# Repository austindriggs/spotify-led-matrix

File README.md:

# Welcome to my first project!

My name is Austin Driggs and I am an Electrical Engineering student at WVU.
Please check out my [LinkedIn](https://www.linkedin.com/in/austindriggs/)!

This project uses an ESP32 microcontroller to display my "Now Playing" songs from Spotify onto an LED matrix panel, along with some added features.

### Purpose

The purpose of this project is to of course learn some new technical skills, but to also practice things related to my career in open sourced coding/projects and project management. I want to document everything along the way to cite sources from what I've learned, decisions I've made, and also to track time. 

## Important Information

### Project Epic

Please see the [Project Epic](https://github.com/austindriggs/spotify-led-matrix/issues/16) for a list of all issues and tasks completed and the order they were completed in.

### Hardware

The KiCAD project is for v7.

### Software

I plan to use python.

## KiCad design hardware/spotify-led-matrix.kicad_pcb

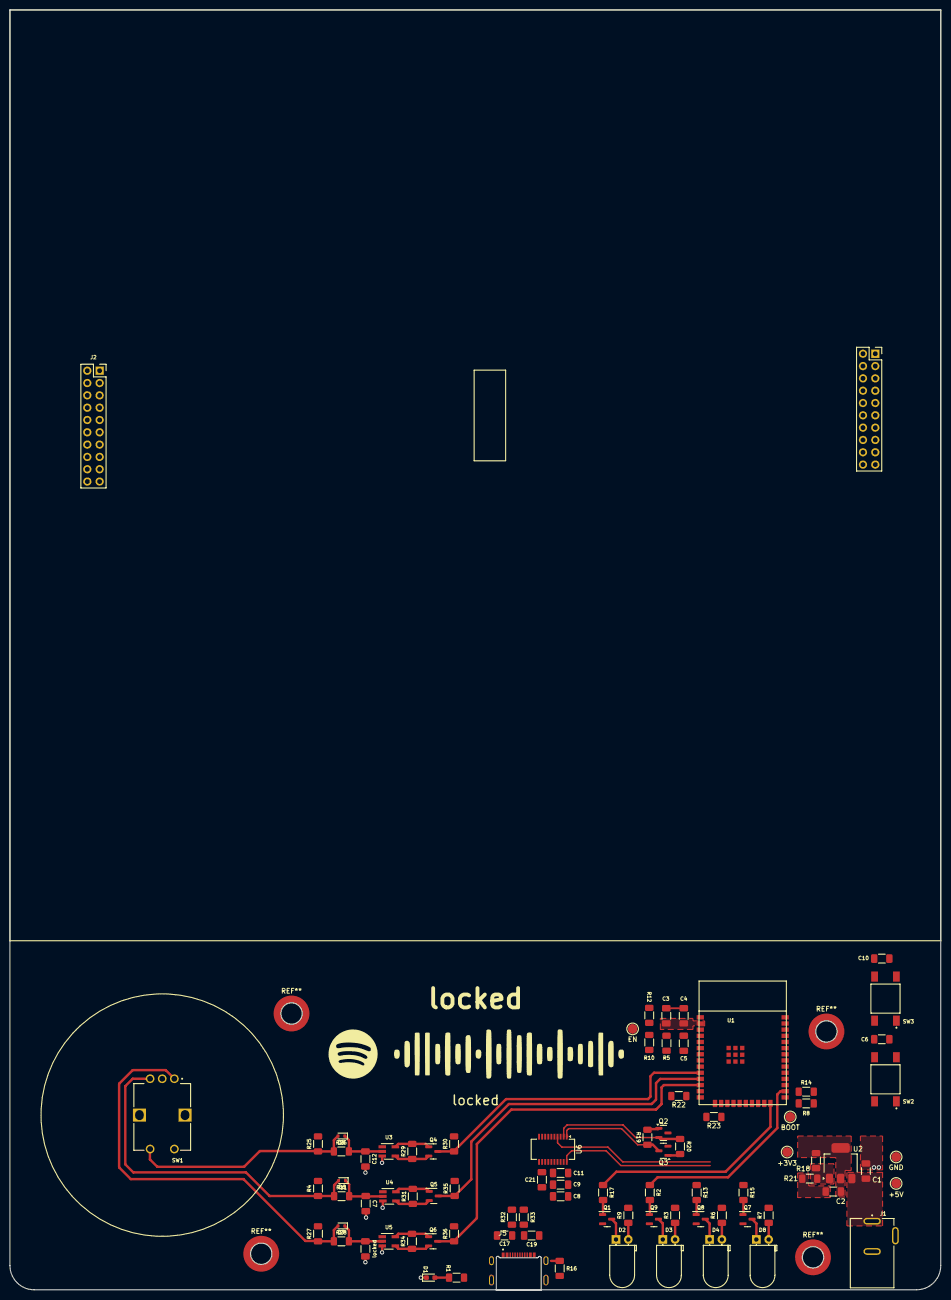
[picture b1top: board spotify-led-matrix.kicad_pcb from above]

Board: 2 copper layers, 192.0 x 264.1 mm, 86 parts (0 on the bottom side), 68 nets.

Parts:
C1, C2: 10uF; C_1206_3216Metric_Pad1.33x1.80mm_HandSolder
C3: 22uF; C_1206_3216Metric_Pad1.33x1.80mm_HandSolder
C4, C6, C7, C10, C12: 0.1uF; C_1206_3216Metric_Pad1.33x1.80mm_HandSolder
C5: 1uF; C_1206_3216Metric_Pad1.33x1.80mm_HandSolder
C8: 4.7uF; C_1206_3216Metric_Pad1.33x1.80mm_HandSolder
C9, C11, C21: 100nF; C_1206_3216Metric_Pad1.33x1.80mm_HandSolder
C17, C19: 47pF; C_1206_3216Metric_Pad1.33x1.80mm_HandSolder
D1: USB; LED_0603_1608Metric_Pad1.05x0.95mm_HandSolder
D2: DEV; LED_D5.0mm_Horizontal_O1.27mm_Z9.0mm
D3: VOLUME; LED_D5.0mm_Horizontal_O1.27mm_Z9.0mm
D4: BRIGHTNESS; LED_D5.0mm_Horizontal_O1.27mm_Z9.0mm
D5, D6, D7: D; D_SOD-523
D8: MODES; LED_D5.0mm_Horizontal_O1.27mm_Z9.0mm
J1: +5V; 54-00166
J2: DISPLAY_IN; PinSocket_2x10_P2.54mm_Vertical
J4: DISPLAY_OUT; PinSocket_2x10_P2.54mm_Vertical
J5: USB_C_Receptacle_USB2.0; MOLEX_2169900003
Q1, Q4, Q5, Q6, Q7, Q8, Q9: IRLML6244TRPBF; SOT-23
Q2, Q3: SS8050-G; SOT-23
R1, R9: 120; R_1206_3216Metric_Pad1.30x1.75mm_HandSolder
R2, R11, R13, R15, R17, R26, R28: 1k; R_1206_3216Metric_Pad1.30x1.75mm_HandSolder
R3, R6, R7: 82; R_1206_3216Metric_Pad1.30x1.75mm_HandSolder
R4, R5, R19, R20, R25, R27, R29, R30, R31, R34, R35, R36: 10k; R_1206_3216Metric_Pad1.30x1.75mm_HandSolder
R8, R10, R12, R14, R22, R23: 22; R_1206_3216Metric_Pad1.30x1.75mm_HandSolder
R16: 0; R_1206_3216Metric_Pad1.30x1.75mm_HandSolder
R18, R21: R_1206_3216Metric_Pad1.30x1.75mm_HandSolder
R32, R33: 27; R_1206_3216Metric_Pad1.30x1.75mm_HandSolder
SW1: MODE_SELECT; CUI_ACZ11BR1E-20FD1-20C
SW2: EN; SW_TL3301DF160QG
SW3: BOOT; SW_TL3301DF160QG
TP1: +5V; TestPoint_Pad_D2.0mm
TP2: GND; TestPoint_Pad_D2.0mm
TP3: +3V3; TestPoint_Pad_D2.0mm
TP4: BOOT; TestPoint_Pad_D2.0mm
TP5: EN; TestPoint_Pad_D2.0mm
U1: ESP32-WROOM-32E
U2: NCP1117-ADJ; SOT-223-3_TabPin2
U3, U4, U5: MC74HC1G14DTT1G; SOT-23-5_HandSoldering
U6: FT231XS-R; SSOP-20_3.9x8.7mm_P0.635mm
locked: 0.1uF; C_1206_3216Metric_Pad1.33x1.80mm_HandSolder

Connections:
+3V3: C2.1, C3.1, C4.1, R5.1, R18.2, R30.2, R35.2, R36.2, TP3.1, U1.2 (VDD), U2.2 (VO)
+5V: C1.1, C8.1, C9.1, C11.1, J1.A, Q4.1 (G), Q5.1 (G), Q6.1 (G), R3.2, R4.2, R6.2, R7.2, R9.2, R25.2, R27.2, R29.2, R31.2, R34.2, TP1.1, U2.3 (VI), U3.5 (VCC), U4.5 (VCC), U5.5 (VCC), U6.15 (VCC)
/B1_IN: J2.5 (B1), J4.8 (G2)
/B2_IN: J2.9 (B2), J4.5 (B1)
/BOOT: R8.1, R14.1, TP4.1, U1.25 (IO0)
/BOOT_AUTO: Q3.2 (S), R8.2
/BOOT_SW: C10.1, R14.2, SW3.2
/BRIGHTNESS: R13.1, U1.28 (IO17)
/BUTTON: Q4.3 (D), R30.1, U1.10 (IO25)
/CS_A: J2.11 (A), U1.31 (IO19)
/CS_B: J2.12 (B), U1.37 (IO23)
/CS_C: J2.13 (C), U1.30 (IO18)
/CS_D: J2.14 (D), U1.29 (IO5)
/CS_E: J2.10 (E), U1.23 (IO15)
/D+: C17.1, J5.A6 (D+), J5.B6 (D+), R32.1
/D-: C19.1, J5.A7 (D-), J5.B7 (D-), R33.1
/DEV: R17.1, U1.24 (IO2)
/DTR: Q3.3 (D), R19.1, U6.1 (~DTR)
/EN: C5.1, R5.2, R10.1, R12.1, TP5.1, U1.3 (EN)
/EN_AUTO: Q2.3 (D), R12.2
/EN_SW: C6.1, R10.2, SW2.2
/G1_IN: J2.4 (G1), J4.7 (R2)
/G2_IN: J2.8 (G2), J4.4 (G1)
/MODES: R15.1, U1.33 (IO21)
/R2_IN: J2.7 (R2), J4.3 (R1)
/ROTARY_A: Q6.3 (D), R36.1, U1.12 (IO27)
/ROTARY_B: Q5.3 (D), R35.1, U1.11 (IO26)
/RTS: Q2.2 (S), R20.1, U6.2 (~RTS)
/RXD0: U1.34 (IO3), U6.4 (RXD)
/SPI_CLK: J2.15 (CLK), R22.2
/SPI_SDA: J2.3 (R1), R23.2
/TXD0: U1.35 (IO1), U6.20 (TXD)
/USBD+: R32.2, U6.11 (USBDP)
/USBD-: R33.2, U6.12 (USBDM)
/VOLUME: R2.1, U1.26 (IO4)
/~LAT: J2.16 (LAT), U1.36 (IO22)
/~OE: J2.17 (~OE), U1.27 (IO16)
GND: C1.2, C2.2, C3.2, C4.2, C5.2, C6.2, C7.2, C8.2, C9.2, C10.2, C11.2, C12.2, C17.2, C19.2, C21.2, D1.1 (K), J1.B, J1.C, J2.6 (GND), J2.18 (GND), J4.6 (GND), J4.18 (GND), J5.A1 (GND), J5.B1 (GND), Q1.2 (S), Q7.2 (S), Q8.2 (S), Q9.2 (S), R16.2, R21.1, SW1.C, SW1.S1, SW2.1, SW3.1, TP2.1, U1.1 (GND), U1.15 (GND), U1.38 (GND), U1.39 (GND), U1.40 (GND), U1.41 (GND), U1.42 (GND), U1.43 (GND), U1.44 (GND), U1.45 (GND), U1.46 (GND), U1.47 (GND), U3.3 (GND), U4.3 (GND), U5.3 (GND), U6.5 (~RI), U6.6 (GND), U6.8 (~DCD), U6.16 (GND), locked.2
unnamed: D1.2 (A), R1.1
unnamed: D2.2 (A), R9.1
unnamed: D2.1 (K), Q1.3 (D)
unnamed: D3.2 (A), R3.1
unnamed: D3.1 (K), Q9.3 (D)
unnamed: D4.2 (A), R6.1
unnamed: D4.1 (K), Q8.3 (D)
unnamed: D5.2 (A), R25.1, R26.1, SW1.S2
unnamed: C12.1, D5.1 (K), R26.2, U3.2
unnamed: D6.2 (A), R4.1, R11.1, SW1.B
unnamed: C7.1, D6.1 (K), R11.2, U4.2
unnamed: D7.2 (A), R27.1, R28.1, SW1.A
unnamed: D7.1 (K), R28.2, U5.2, locked.1
unnamed: D8.2 (A), R7.1
unnamed: D8.1 (K), Q7.3 (D)
unnamed: J5.S1 (SHIELD), R16.1
unnamed: Q1.1 (G), R17.2
unnamed: Q2.1 (G), R19.2
unnamed: Q3.1 (G), R20.2
unnamed: Q4.2 (S), R29.1, U3.4
unnamed: Q5.2 (S), R31.1, U4.4
unnamed: Q6.2 (S), R34.1, U5.4
unnamed: Q7.1 (G), R15.2
unnamed: Q8.1 (G), R13.2
unnamed: Q9.1 (G), R2.2
unnamed: R23.1, U1.16 (IO13)
unnamed: R22.1, U1.13 (IO14)
unnamed: R18.1, R21.2, U2.1 (ADJ)
unnamed: C21.1, U6.3 (VCCIO), U6.13 (3V3OUT), U6.14 (~RESET)
VBUS: J5.A4 (VBUS), J5.B4 (VBUS), R1.2

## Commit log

2023-09-13 Update issue templates
2023-10-04 Added KiCad files for initial circuit design.
2023-10-04 Added pdf of schematic
2023-10-14 Added some connections for SPI communication to display
2023-10-14 Saved PDF to reflect changes to schematic
2023-11-01 Only updated PDF to show the current schematic.
2023-11-10 Replaced USB to UART converter and updated schematic format
2023-11-13 Only updated schematic.pdf to show updated circuit 231113.
2023-11-14 Re-updated schematic.pdf to show updated circuit 231113.
2023-11-15 Added gitignore
2023-11-15 Finished schematic and picked out most parts
2023-11-15 Updated schematic
2023-11-15 Working out gitignore issues.
2023-11-15 Updated gitignore
2023-11-15 Cleaned up file organization
2023-12-02 Cleaned up a lot and started pcb layout
2024-01-09 Reorganized files again: Wanted to push to backup everything.
2024-01-31 worked on the layout
2024-01-31 more layout stuff
2024-01-31 locked layouts
2024-01-31 locked more
2024-01-31 added step files
2024-02-01 layout stuff and .gitignore update
2024-02-01 removed files
2024-02-01 added hardware-layout.pdf and started power supply swap
2024-02-04 backup
2024-04-06 reformatted schematic and changed parts: - added new voltage regulator: 1117 adjustable (jellybean) - added temp/volt/cur sensor LTC2990 - changed usb to uart IC to SSOP20 footprint - created and add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
2024-04-17 lots of changes: working on finalizing everything!
2024-06-27 update?
2026-05-08 backup refs from laptop on 2026-04-08
